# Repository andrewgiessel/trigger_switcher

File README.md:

trigger_switcher
================

Arduino Code to multiplex a single trigger through a series of digital lines.

`blink_switch` and `led_and_serial` are early drafts of getting the logic working.  `passthru` is the final code we'll be using.

We're using a teensy 2.0++ board, and the PCB files are for Eagle.

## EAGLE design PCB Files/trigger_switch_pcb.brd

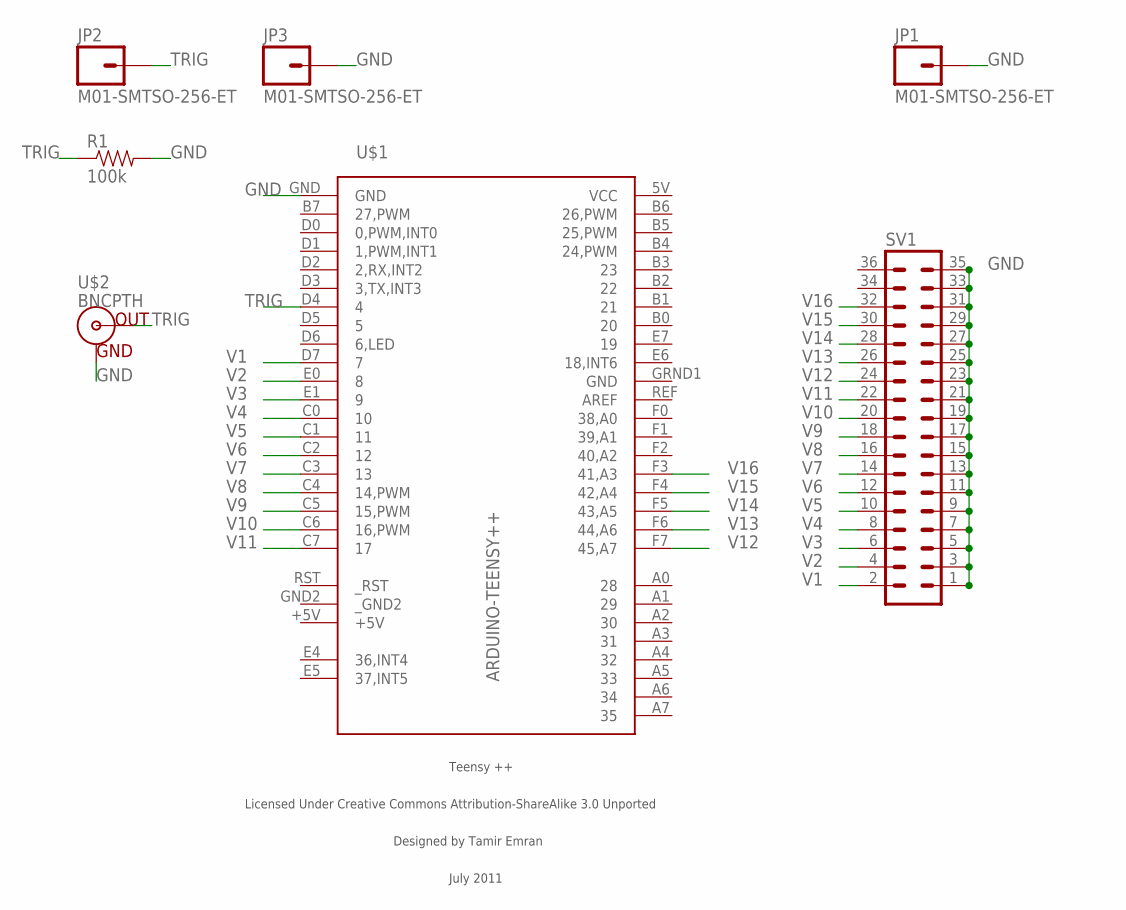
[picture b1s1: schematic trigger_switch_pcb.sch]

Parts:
JP1, JP2, JP3: M01-SMTSO-256-ET; SMTSO-256-ET
R1: 100k; AXIAL-0.5
SV1: MA18-2
U$1: ARDUINO-TEENSY++; TEENSY++
U$2: BNCPTH; BNC

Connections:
+5V: U$1.+5V
GND: JP1.P$1, JP3.P$1, R1.P$2 (2), SV1.1, SV1.3, SV1.5, SV1.7, SV1.9, SV1.11, SV1.13, SV1.15, SV1.17, SV1.19, SV1.21, SV1.23, SV1.25, SV1.27, SV1.29, SV1.31, SV1.33, SV1.35, U$1.GND, U$1.GRND1 (GND), U$2.GND
TRIG: JP2.P$1, R1.P$1 (1), U$1.D4 (4), U$2.S (OUT)
V1: SV1.2, U$1.D7 (7)
V2: SV1.4, U$1.E0 (8)
V3: SV1.6, U$1.E1 (9)
V4: SV1.8, U$1.C0 (10)
V5: SV1.10, U$1.C1 (11)
V6: SV1.12, U$1.C2 (12)
V7: SV1.14, U$1.C3 (13)
V8: SV1.16, U$1.C4 (14,PWM)
V9: SV1.18, U$1.C5 (15,PWM)
V10: SV1.20, U$1.C6 (16,PWM)
V11: SV1.22, U$1.C7 (17)
V12: SV1.24, U$1.F7 (45,A7)
V13: SV1.26, U$1.F6 (44,A6)
V14: SV1.28, U$1.F5 (43,A5)
V15: SV1.30, U$1.F4 (42,A4)
V16: SV1.32, U$1.F3 (41,A3)
VCC: U$1.5V (VCC)
_GND2: U$1.GND2 (_GND2)

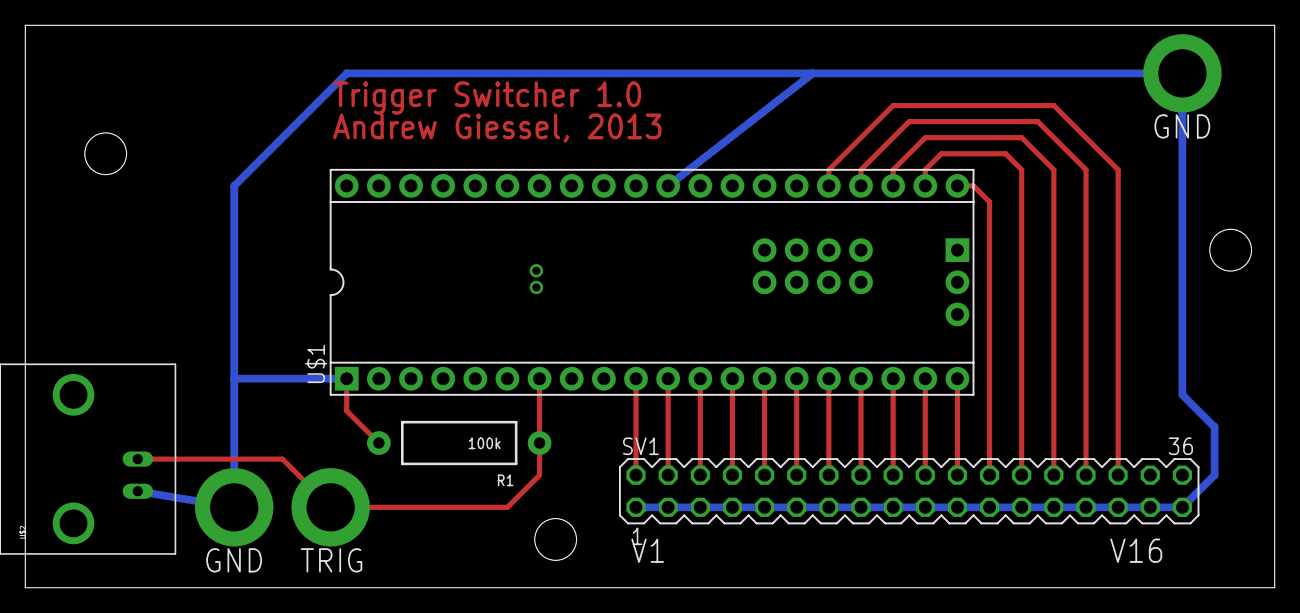
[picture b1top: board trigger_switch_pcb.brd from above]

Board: 2 copper layers, 98.7 x 44.4 mm, 10 parts (0 on the bottom side), 18 nets.

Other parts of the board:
U$3, U$4, U$6: STAND-OFF

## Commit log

2013-08-11 initial commit
    simple example with an LED
    the particular pin depends on the device. working with a teensy2.0++
    and a duemilanove
2013-08-11 cleanup
2013-08-11 adding pinout
2013-08-11 blink_val update
    getting weird bugs where it just keeps flashing, instead of only
    flashing when triggered from +5V… bad hardware? bad breadboard?
    trying to switch on single chars --- so have to have the case statement
2013-08-12 Update blink_switch.ino
    fixed switch statement (needed break; after every case!)
    also, made inputVal a <char> for the switch
2013-08-12 Create passthru.ino
    still using single chars over serial...
2013-08-12 Update passthru.ino
    broke out update thru pin to seperate function
    added 10 ms delay to deal with switch bounce, remove later
    note that strings terminate with \0 - had to add a case statement to treat it as a '0'
    added code to swap pins (valve 0 on/off at the same time as other valve off/on)
    used memset to set all the memory in the the triggerSequence buffer to '0'
2013-08-15 initial commit of PCB eagle files
    One for the schematic, one for the board
2013-08-15 updated .gitignore for EAGLE temp files
2013-08-15 update to wiring diagram
    i think i have the board schematic done! All grounds on the bottom,
    all signals on the top
2013-08-15 Final? Changes to board
    added standoffs, resized board
2013-08-15 fixed text typos
2013-08-15 final changes to .brd
2013-08-15 SHRINK
2013-08-21 adding manual switch via serial
    Lots of changes here to make the default valve (generally '0') to be
    whatever you want.
    * renamed 'updateThruPin() to char2pin(), and it returns a value rather
    than change the global variables.
    * added pin2char() to do the reverse, which is used for setting the
    default values in the state sequence.

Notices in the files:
parts and their libraries:
teensypp: Licensed Under Creative Commons
SparkFun-Resistors: Licensing: CC v3.0 Share-Alike You are welcome to use this library for commercial purposes.
teensypp: Licensed Under Creative Commons Attribution-ShareAlike 3.0 Unported
